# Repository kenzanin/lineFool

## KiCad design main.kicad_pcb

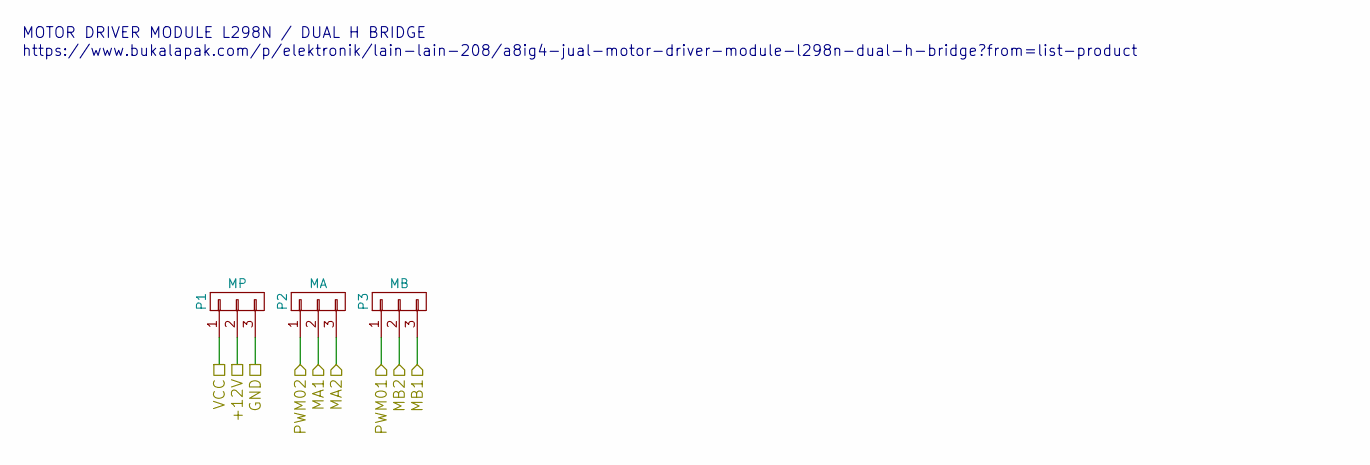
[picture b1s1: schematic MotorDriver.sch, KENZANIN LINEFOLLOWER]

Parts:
P1: MP; Pin_Header_Straight_1x03
P2: MA; Pin_Header_Straight_1x03
P3: MB; Pin_Header_Straight_1x03

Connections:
/Controller/MA1: P2.2; also elsewhere on the board
/Controller/MA2: P2.3; also elsewhere on the board
/Controller/MB1: P3.3; also elsewhere on the board
/Controller/MB2: P3.2; also elsewhere on the board
/Controller/PWM01: P3.1; also elsewhere on the board
/Controller/PWM02: P2.1; also elsewhere on the board
/Controller/VCC: P1.1; also elsewhere on the board
/MotorDriver/+12V: P1.2; also elsewhere on the board
GND: P1.3; also elsewhere on the board

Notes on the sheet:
MOTOR DRIVER MODULE L298N / DUAL H BRIDGE
https://www.bukalapak.com/p/elektronik/lain-lain-208/a8ig4-jual-motor-driver-module-l298n-dual-h-bridge?from=list-product

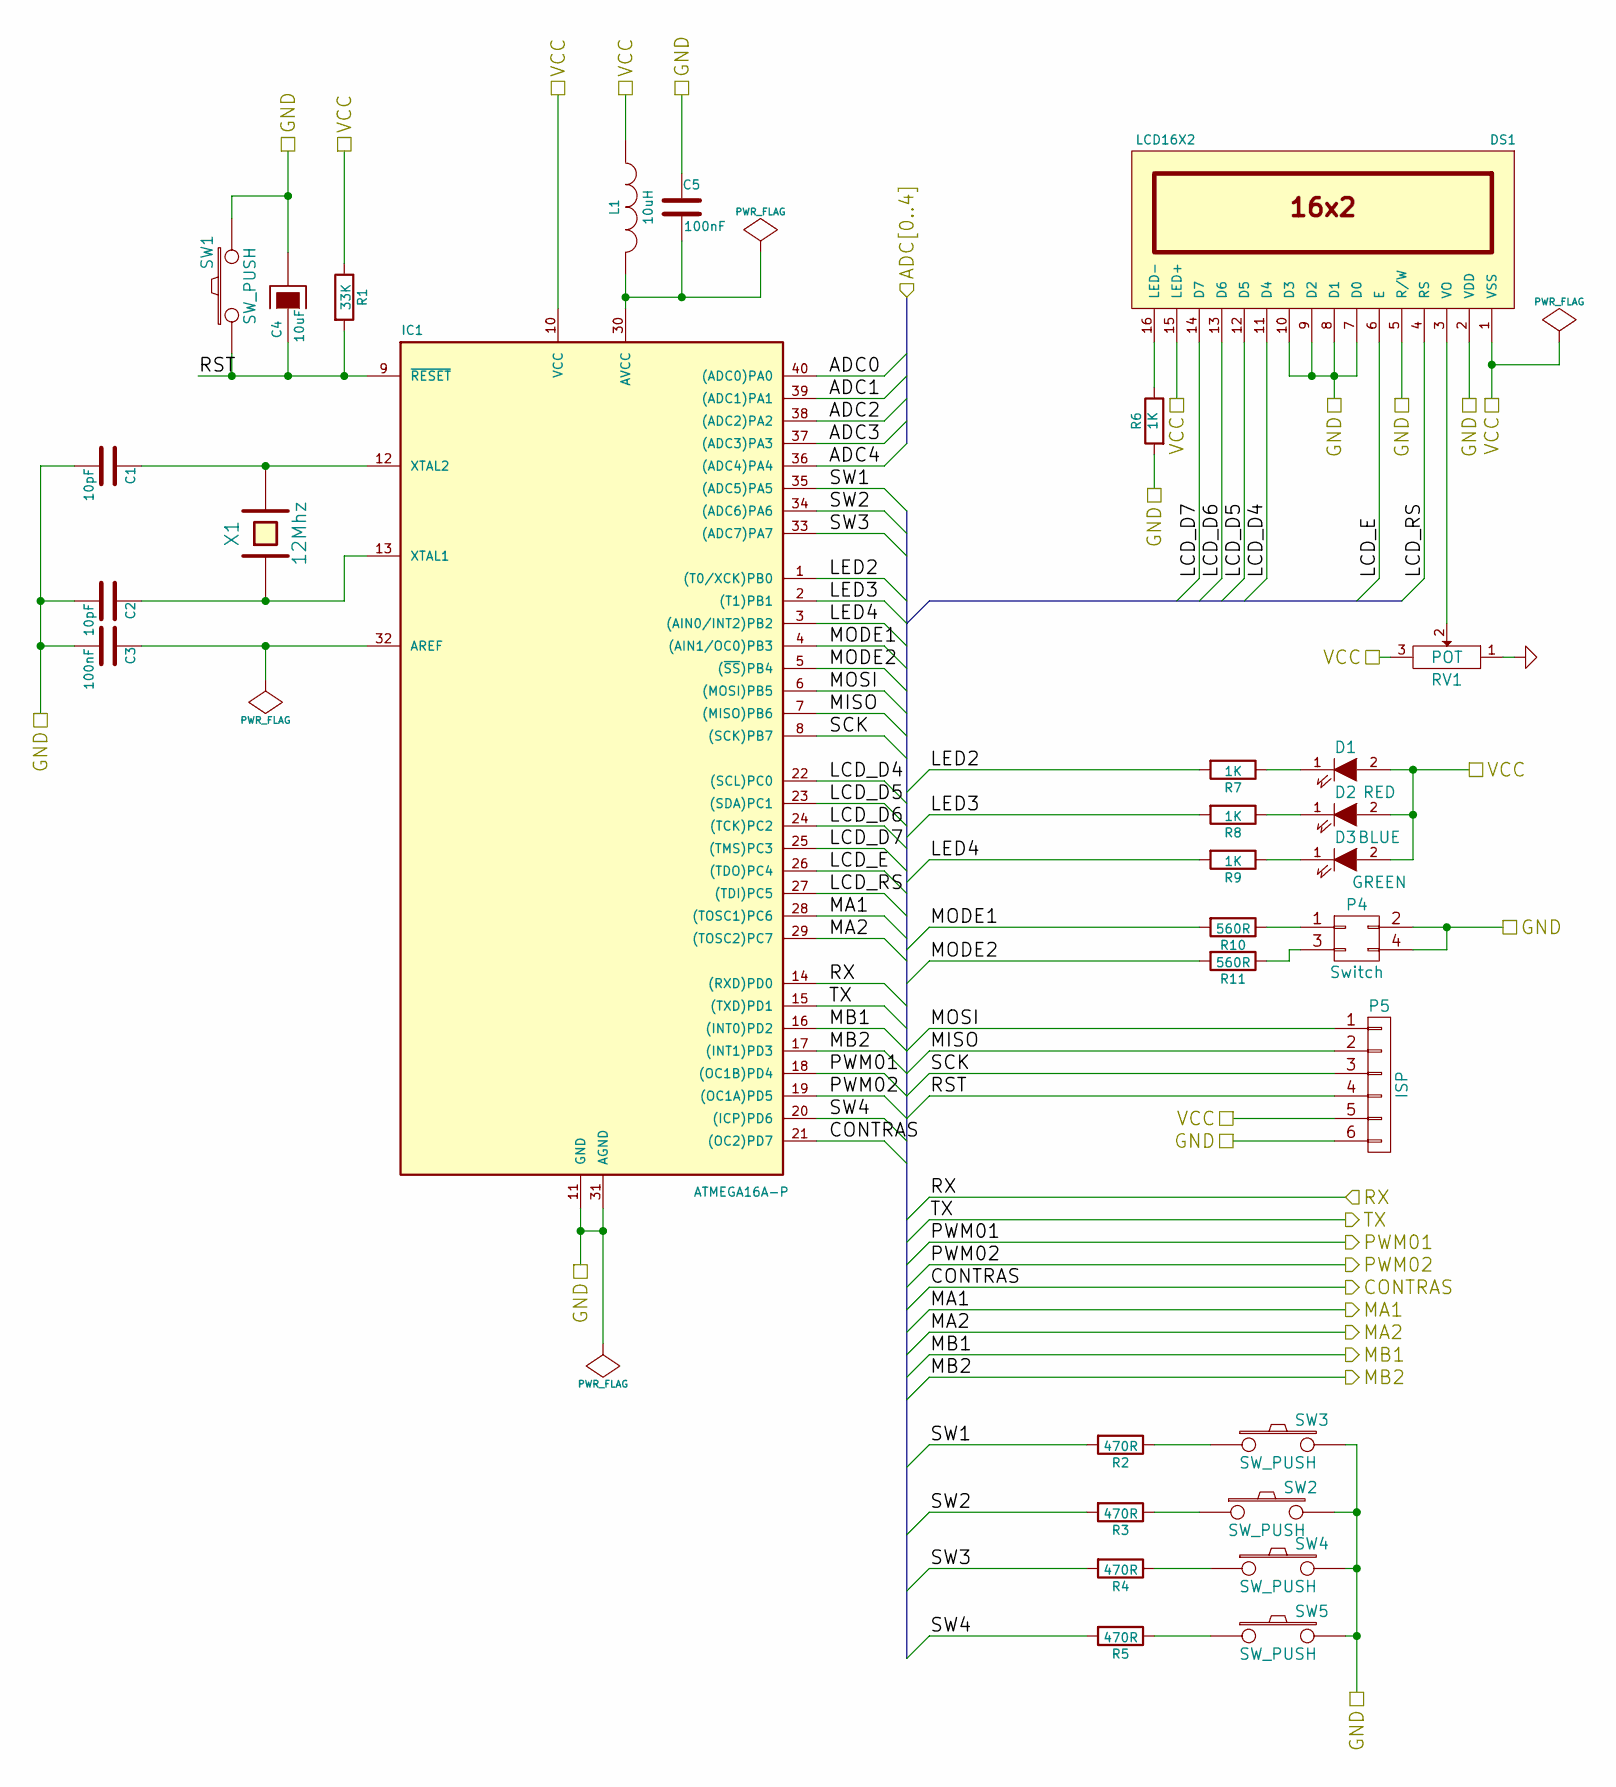
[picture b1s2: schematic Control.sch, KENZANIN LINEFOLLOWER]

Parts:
C1, C2: 10pF; C_0805_HandSoldering
C3, C5: 100nF; C_0805_HandSoldering
C4: 10uF; Capacitor5x6RM2.5
D1: RED; LED-3MM
D2: BLUE; LED-3MM
D3: GREEN; LED-3MM
DS1: LCD16X2; TUXGR_16X2_R2
IC1: ATMEGA16A-P; DIP-40__600_ELL
L1: 10uH; Capacitor5x6RM2.5
P4: Switch; Pin_Header_Straight_2x02
P5: ISP; Pin_Header_Straight_1x06
R1: 33K; R_0805_HandSoldering
R2, R3, R4, R5: 470R; R_0805_HandSoldering
R6: 1K; Resistor_Horizontal_RM15mm
R7, R8, R9: 1K; R_0805_HandSoldering
R10, R11: 560R; R_0805_HandSoldering
RV1: POT; Potentiometer_Triwood_RM-065
SW1, SW2, SW3, SW4, SW5: SW_PUSH; Pin_Header_Straight_1x02
X1: 12Mhz; Crystal_HC49-U_Vertical

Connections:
/Controller/ADC0: IC1.40 ((ADC0)PA0); also elsewhere on the board
/Controller/ADC1: IC1.39 ((ADC1)PA1); also elsewhere on the board
/Controller/ADC2: IC1.38 ((ADC2)PA2); also elsewhere on the board
/Controller/ADC3: IC1.37 ((ADC3)PA3); also elsewhere on the board
/Controller/ADC4: IC1.36 ((ADC4)PA4); also elsewhere on the board
/Controller/CONTRAS: IC1.21 ((OC2)PD7); also elsewhere on the board
/Controller/LCD_D4: DS1.11 (D4), IC1.22 ((SCL)PC0)
/Controller/LCD_D5: DS1.12 (D5), IC1.23 ((SDA)PC1)
/Controller/LCD_D6: DS1.13 (D6), IC1.24 ((TCK)PC2)
/Controller/LCD_D7: DS1.14 (D7), IC1.25 ((TMS)PC3)
/Controller/LCD_E: DS1.6 (E), IC1.26 ((TDO)PC4)
/Controller/LCD_RS: DS1.4 (RS), IC1.27 ((TDI)PC5)
/Controller/LED2: IC1.1 ((T0/XCK)PB0), R7.2
/Controller/LED3: IC1.2 ((T1)PB1), R8.2
/Controller/LED4: IC1.3 ((AIN0/INT2)PB2), R9.2
/Controller/MA1: IC1.28 ((TOSC1)PC6); also elsewhere on the board
/Controller/MA2: IC1.29 ((TOSC2)PC7); also elsewhere on the board
/Controller/MB1: IC1.16 ((INT0)PD2); also elsewhere on the board
/Controller/MB2: IC1.17 ((INT1)PD3); also elsewhere on the board
/Controller/MISO: IC1.7 ((MISO)PB6), P5.2
/Controller/MODE1: IC1.4 ((AIN1/OC0)PB3), R10.2
/Controller/MODE2: IC1.5 ((~SS~)PB4), R11.2
/Controller/MOSI: IC1.6 ((MOSI)PB5), P5.1
/Controller/PWM01: IC1.18 ((OC1B)PD4); also elsewhere on the board
/Controller/PWM02: IC1.19 ((OC1A)PD5); also elsewhere on the board
/Controller/RST: C4.1, IC1.9 (~RESET), P5.4, R1.2, SW1.1
/Controller/RX: IC1.14 ((RXD)PD0); also elsewhere on the board
/Controller/SCK: IC1.8 ((SCK)PB7), P5.3
/Controller/SW1: IC1.35 ((ADC5)PA5), R2.2
/Controller/SW2: IC1.34 ((ADC6)PA6), R3.2
/Controller/SW3: IC1.33 ((ADC7)PA7), R4.2
/Controller/SW4: IC1.20 ((ICP)PD6), R5.2
/Controller/TX: IC1.15 ((TXD)PD1); also elsewhere on the board
/Controller/VCC: D1.2 (A), D2.2 (A), D3.2 (A), DS1.1 (VSS), DS1.15 (LED+), IC1.10 (VCC), L1.1, P5.5, R1.1, RV1.3; also elsewhere on the board
GND: C1.2, C2.2, C3.2, C4.2, C5.1, DS1.2 (VDD), DS1.5 (R/W), DS1.7 (D0), DS1.8 (D1), DS1.9 (D2), DS1.10 (D3), IC1.11 (GND), IC1.31 (AGND), P4.2, P4.4, P5.6, R6.2, RV1.1, SW1.2, SW2.2, SW3.2, SW4.2, SW5.2; also elsewhere on the board
unnamed: C1.1, IC1.12 (XTAL2), X1.2
unnamed: C2.1, IC1.13 (XTAL1), X1.1
unnamed: C3.1, IC1.32 (AREF)
unnamed: C5.2, IC1.30 (AVCC), L1.2
unnamed: D1.1 (K), R7.1
unnamed: D2.1 (K), R8.1
unnamed: D3.1 (K), R9.1
unnamed: DS1.3 (VO), RV1.2
unnamed: DS1.16 (LED-), R6.1
unnamed: P4.1, R10.1
unnamed: P4.3, R11.1
unnamed: R2.1, SW3.1
unnamed: R3.1, SW2.1
unnamed: R4.1, SW4.1
unnamed: R5.1, SW5.1

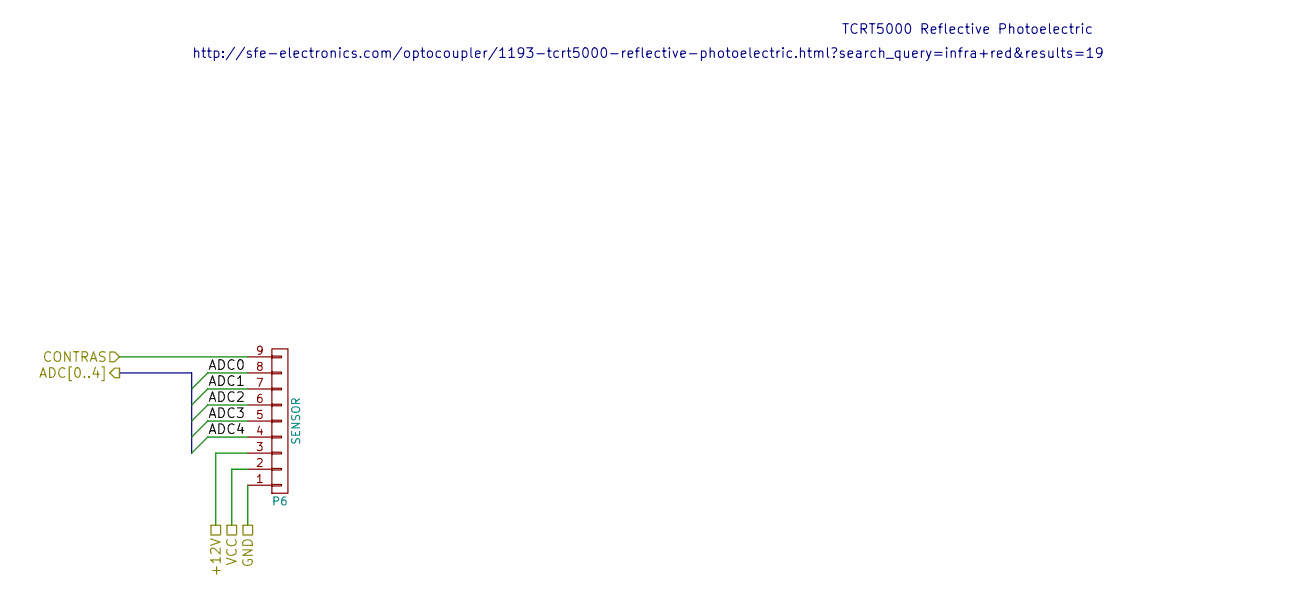
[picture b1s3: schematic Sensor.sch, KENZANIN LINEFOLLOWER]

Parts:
P6: SENSOR; Pin_Header_Straight_1x09

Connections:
/Controller/ADC0: P6.8; also elsewhere on the board
/Controller/ADC1: P6.7; also elsewhere on the board
/Controller/ADC2: P6.6; also elsewhere on the board
/Controller/ADC3: P6.5; also elsewhere on the board
/Controller/ADC4: P6.4; also elsewhere on the board
/Controller/CONTRAS: P6.9; also elsewhere on the board
/Controller/VCC: P6.2; also elsewhere on the board
/MotorDriver/+12V: P6.3; also elsewhere on the board
GND: P6.1; also elsewhere on the board

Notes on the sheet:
TCRT5000 Reflective Photoelectric
http://sfe-electronics.com/optocoupler/1193-tcrt5000-reflective-photoelectric.html?search_query=infra+red&results=19

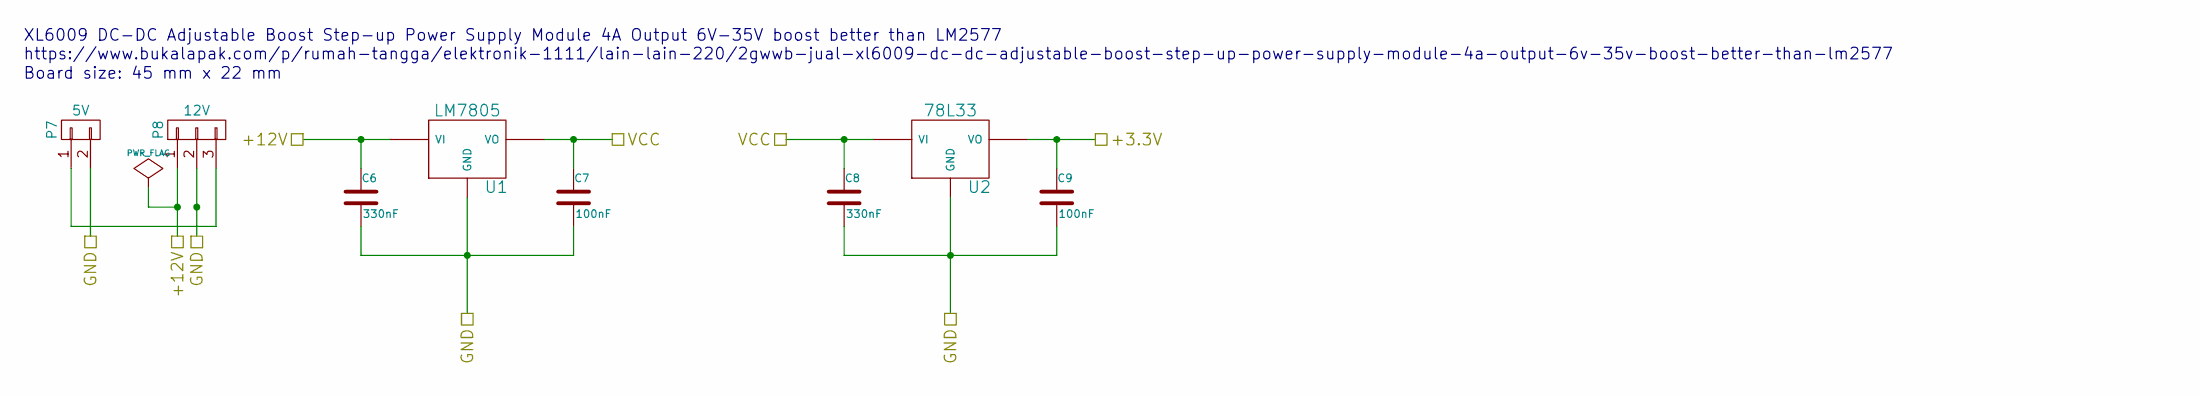
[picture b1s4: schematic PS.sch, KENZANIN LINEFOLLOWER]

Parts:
C6, C8: 330nF; C_0805_HandSoldering
C7, C9: 100nF; C_0805_HandSoldering
P7: 5V; Socket_Strip_Straight_1x02
P8: 12V; Pin_Header_Straight_1x03
U1: LM7805; LM78XX-TO92
U2: 78L33; LM78XX-TO92

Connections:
/Controller/VCC: C7.1, C8.1, U1.VO, U2.VI; also elsewhere on the board
/Debugger/+3.3V: C9.1, U2.VO; also elsewhere on the board
/MotorDriver/+12V: C6.1, P8.1, U1.VI; also elsewhere on the board
GND: C6.2, C7.2, C8.2, C9.2, P7.2, P8.2, U1.GND, U2.GND; also elsewhere on the board
unnamed: P7.1, P8.3

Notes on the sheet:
XL6009 DC-DC Adjustable Boost Step-up Power Supply Module 4A Output 6V-35V boost better than LM2577 https://www.bukalapak.com/p/rumah-tangga/elektronik-1111/lain-lain-220/2gwwb-jual-xl6009-dc-dc-adjustable-boost-step-up-power-supply-module-4a-output-6v-35v-boost-better-than-lm2577
Board size: 45 mm x 22 mm

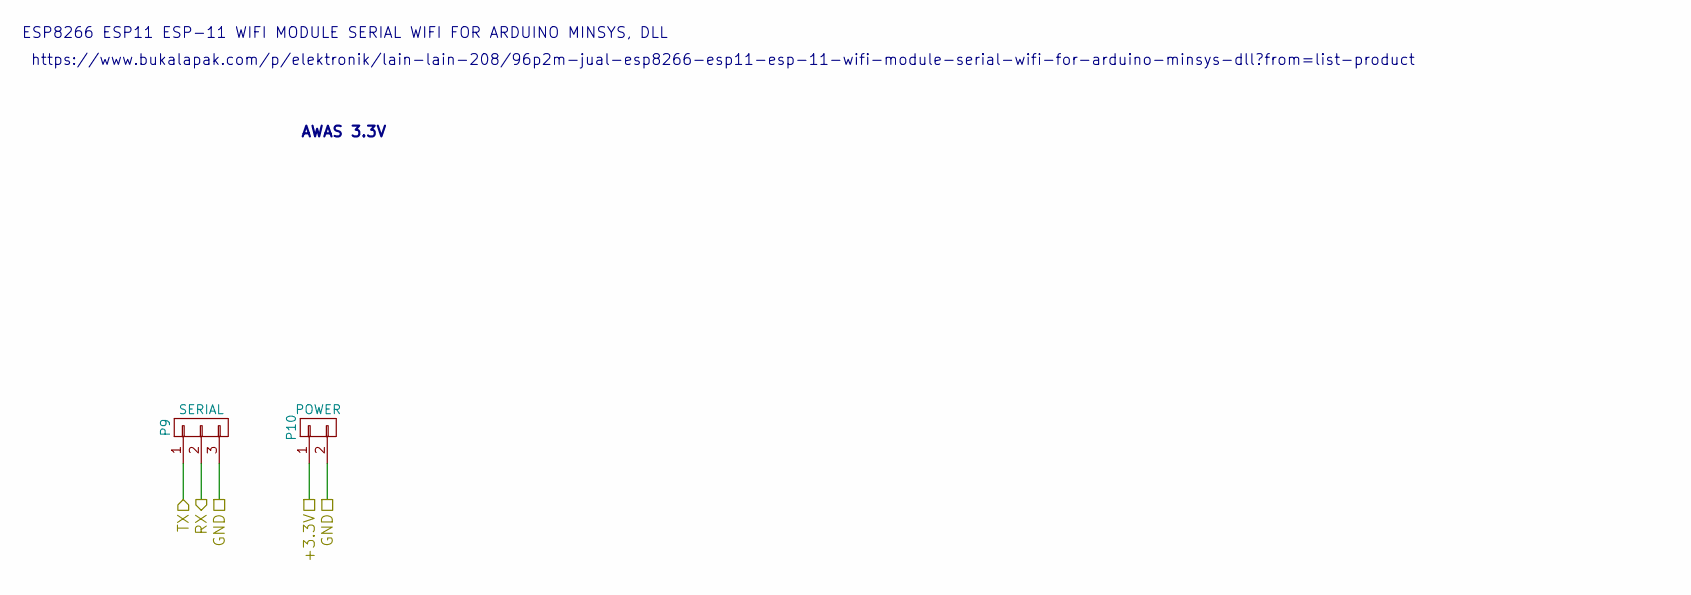
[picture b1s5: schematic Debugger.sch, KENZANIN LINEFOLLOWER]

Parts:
P9: SERIAL; Pin_Header_Straight_1x03
P10: POWER; Pin_Header_Straight_1x02

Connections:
/Controller/RX: P9.2; also elsewhere on the board
/Controller/TX: P9.1; also elsewhere on the board
/Debugger/+3.3V: P10.1; also elsewhere on the board
GND: P9.3, P10.2; also elsewhere on the board

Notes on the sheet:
https://www.bukalapak.com/p/elektronik/lain-lain-208/96p2m-jual-esp8266-esp11-esp-11-wifi-module-serial-wifi-for-arduino-minsys-dll?from=list-product
ESP8266 ESP11 ESP-11 WIFI MODULE SERIAL WIFI FOR ARDUINO MINSYS, DLL
AWAS 3.3V

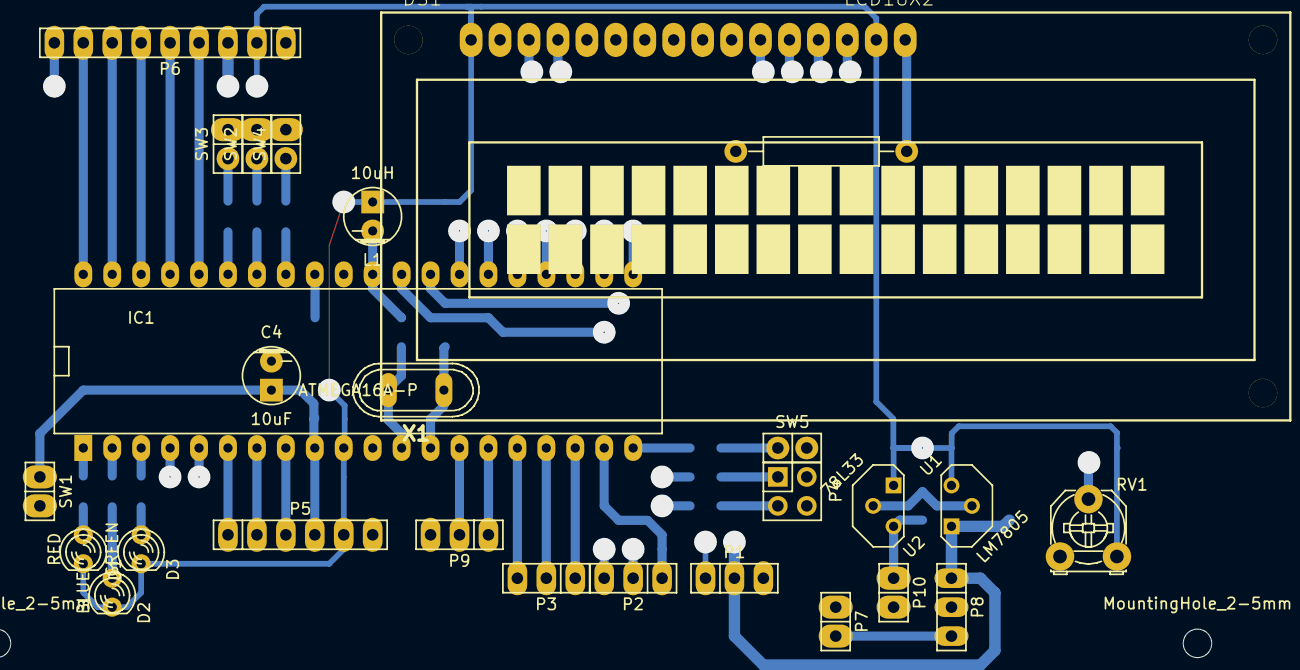
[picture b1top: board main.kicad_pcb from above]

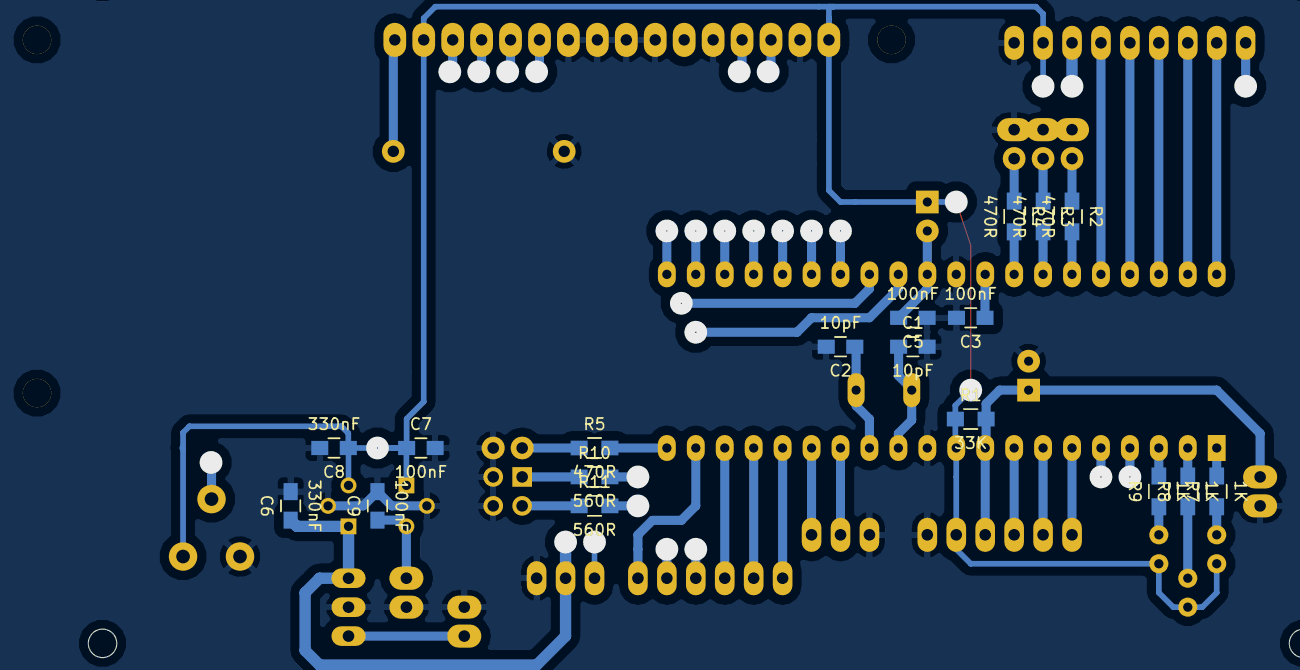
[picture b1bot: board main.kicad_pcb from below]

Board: 2 copper layers, 49 parts (18 on the bottom side), 53 nets.

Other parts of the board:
MountingHole_2-5mm, MountingHole_2-5mm#2, MountingHole_2-5mm#3, MountingHole_2-5mm#4: VAL**; MountingHole_2-5mm

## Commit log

2015-06-25 First Commit new file: Control.sch new file: DSC_1063.jpg new file: Debugger.sch new file: IMG_0825.jpg new file: MotorDriver.sch new file: PS.sch new file: Sensor.sch
2015-06-25 Changes to be committed: deleted: Control.bak deleted: MotorDriver.bak deleted: PS.bak deleted: Sensor.bak deleted: main.bak
2015-06-25 Changes to be committed: new file: TCRT5000.mod new file: tcrt5000.lib
2015-06-25 Changes to be committed: deleted: XL6009-Schematic-Diagram.pdf
2015-06-25 Changes to be committed: deleted: Debugger.bak
2015-06-27 Changes to be committed: new file: 78LXXSOT89.pdf modified: Control.sch modified: Debugger.sch modified: MotorDriver.sch modified: PS.sch modified: Sensor.sch new file: XL6009-Schematic-Diagram.pdf m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
